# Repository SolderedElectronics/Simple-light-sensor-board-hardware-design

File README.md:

# Simple light sensor board Hardware Design

## About the Product

|  |
| :----------------------------------------------------------: |
| [Buy Simple light sensor board](https://www.solde.red/333046) |

Light is one of the most important things in the life of most living beings. Because of this, it is common to work with light sensors when learning about electronics. The simple light sensor features a light-dependent resistor (LDR) and a sensor on a small breakout board for easier connection. As the name suggests, the LDR will change its resistance depending on the amount of light it’s exposed to. The amount of light and resistance are inversely proportional. The more light it’s exposed to, the less resistance it will have. Thus, if there’s more light, the board will have a resistance of a few hundred Ohms. If the resistor is in the dark, it will have a resistance of several thousand Ohms.

The main benefit of this board is ability to give analog and digital output. By setting the potenciometer on the board, you are able to get digital signal at the DO pin when signal crosses certain value, while analog values will be present on the AO pin at all times.

---

## Repository Contents

This repository contains all design files for Simple light sensor board, organized as follows:

- **`CAD` folder**: Contains KiCAD design files, including:
  - Schematics
  - PCB layout
  - Panel PCB layout
  - Source 3D files in Fusion360, if any
  - All files are sorted by version with a detailed change log.
- **`OUTPUTS` folder**: Includes all production-ready files, such as:
  - Bill of Materials (BOM) and interactive BOM (iBOM)
  - PDF versions of schematics
  - 3D `.step` file of the board
  - 3D-printable models
  - Gerber files for PCB manufacturing
  - Image of the pinout of the board
  - Product image
  - Compliance, legal and generic sales documents

Refer to the `Change Log` in the CAD folder for details about updates between versions.

---

## Learn More About the Product

Beyond the repository, explore the following resources:

### Soldered Verify

The **Soldered Verify** system ensures every board you purchase from Soldered is fully functional. It also provides access to exclusive test data for your product. To get started, find the unique Soldered Verify ID on your product's packaging and enter the ID on the [Soldered Verify page](https://soldered.com/verify/) to access test results and additional product details.

### Soldered Community

Soldered Community is your go-to place for technical support. Our engineers track and answer all questions posted there, and it’s a great space for the maker community. Get answers to your questions and solutions for your challenges at [Soldered Community](https://soldered.com/community).

### solde.red

solde.red is an ultimate URL shortener and information hub. Access it by typing solde.red/ followed by your product SKU, e.g., [solde.red/333000](https://solde.red/333000), to find getting-started guides, datasheets, open-source hardware and software files, certifications, images, pinouts, and more. Read more about the shortener [here](https://solde.red/info/).

---

## Contributing

Contributions are welcome! Here’s how you can get involved:

- Submit pull requests to enhance the design or fix issues.
- Report bugs or problems by opening an issue.

We encourage community collaboration to make this product even better.

---

## About Soldered

[Soldered for Makers](https://soldered.com) specializes in designing and manufacturing electronic products tailored for enthusiasts, ranging from hobbyists to professionals. Our portfolio includes electronic boards, sensors, and actuators that are widely utilized in fields such as microelectronics, mechatronics, robotics, programming, and IoT. Every product we offer is designed in-house and built upon open-source hardware and software platforms. Proudly certified and manufactured within the European Union, our catalog likely includes the product you need for your project.

We complement these products with comprehensive tutorials and manuals, product descriptions, schematics, programming codes, and project examples. Our round-the-clock [customer and technical support](https://soldered.com/community) is available for all our products, irrespective of the sales channel. Soldered’s success and services reflect our maker community’s unwavering [trust](https://www.trustpilot.com/review/soldered.com), for which we are deeply grateful. Join our community and create using Soldered products.

---

## License

All Soldered open-source hardware (OSH) is under The TAPR Open Hardware License. Read more in the LICENSE file located in this repository.

**Disclaimer:**

No warranty - all designs in this repository are distributed in the hope that they will be useful, but without any warranty. They are provided "AS IS", therefore without warranty of any kind, either expressed or implied. The entire quality and performance of what you do with the contents of this repository are your responsibility. In no event Soldered Electronics will be liable for your damages, or losses, including any general, special, incidental, or consequential damage arising out of the use or inability to use the contents of this repository. 

---

## Have fun!

Thank you for your support from your fellow makers at Soldered Electronics.

Happy Making!

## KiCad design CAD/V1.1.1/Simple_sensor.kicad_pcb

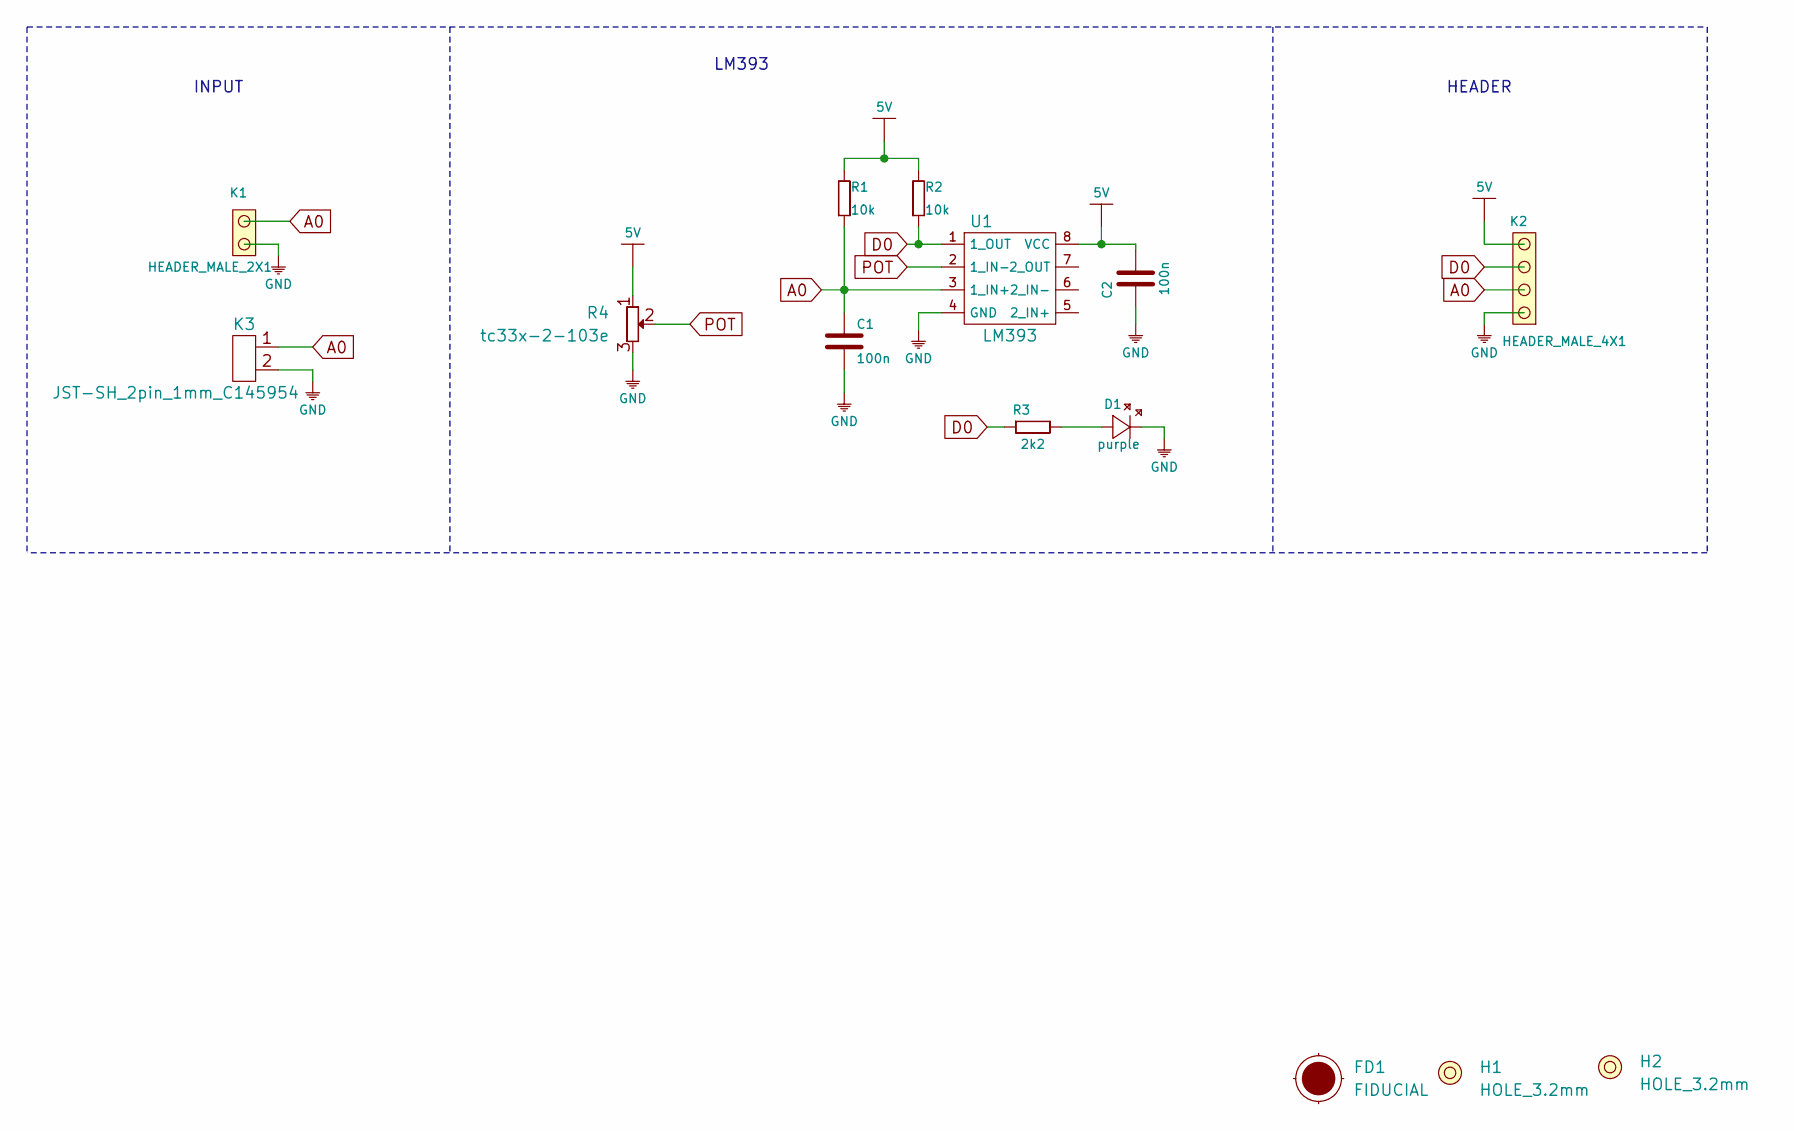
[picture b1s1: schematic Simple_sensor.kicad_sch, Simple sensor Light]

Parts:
C1, C2: 100n; 0603C
D1: purple; 0402LED
FD1: FIDUCIAL; FIDUCIAL_23
H1, H2: HOLE_3.2mm
K1: HEADER_MALE_2X1
K2: HEADER_MALE_4X1
K3: JST-SH_2pin_1mm_C145954
R1, R2: 10k; 0603R
R3: 2k2; 0402R
R4: tc33x-2-103e
U1: LM393; SOIC−8

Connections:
5V: C2.2, K2.4, R1.2, R2.2, R4.1, U1.8 (VCC)
A0: C1.2, K1.2, K2.2, K3.1, R1.1, U1.3 (1_IN+)
D0: K2.3, R2.1, R3.1, U1.1 (1_OUT)
GND: C1.1, C2.1, D1.2 (K), K1.1, K2.1, K3.2, R4.3, U1.4 (GND)
unnamed: D1.1 (A), R3.2
POT: R4.2, U1.2 (1_IN-)

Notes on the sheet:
HEADER
LM393
INPUT

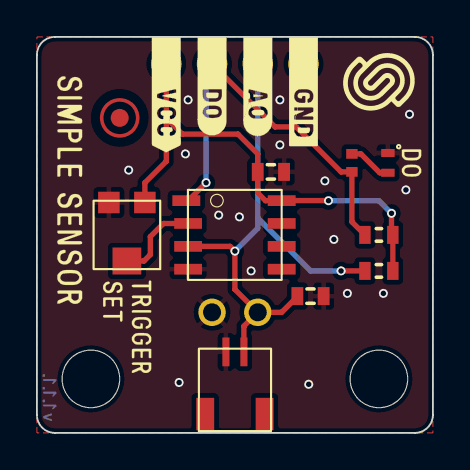
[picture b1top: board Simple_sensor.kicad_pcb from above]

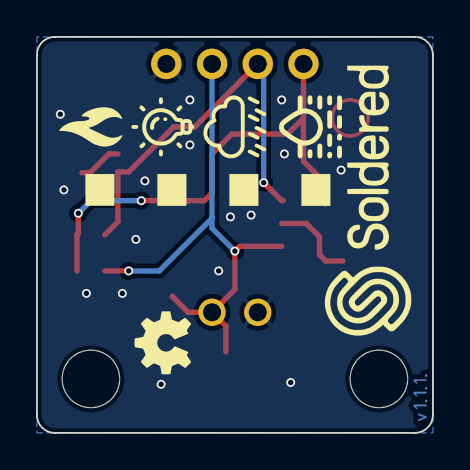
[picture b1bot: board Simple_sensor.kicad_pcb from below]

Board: 2 copper layers, 22.0 x 22.0 mm, 14 parts (2 on the bottom side), 6 nets.

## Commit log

2022-08-06 Updating open source files.
